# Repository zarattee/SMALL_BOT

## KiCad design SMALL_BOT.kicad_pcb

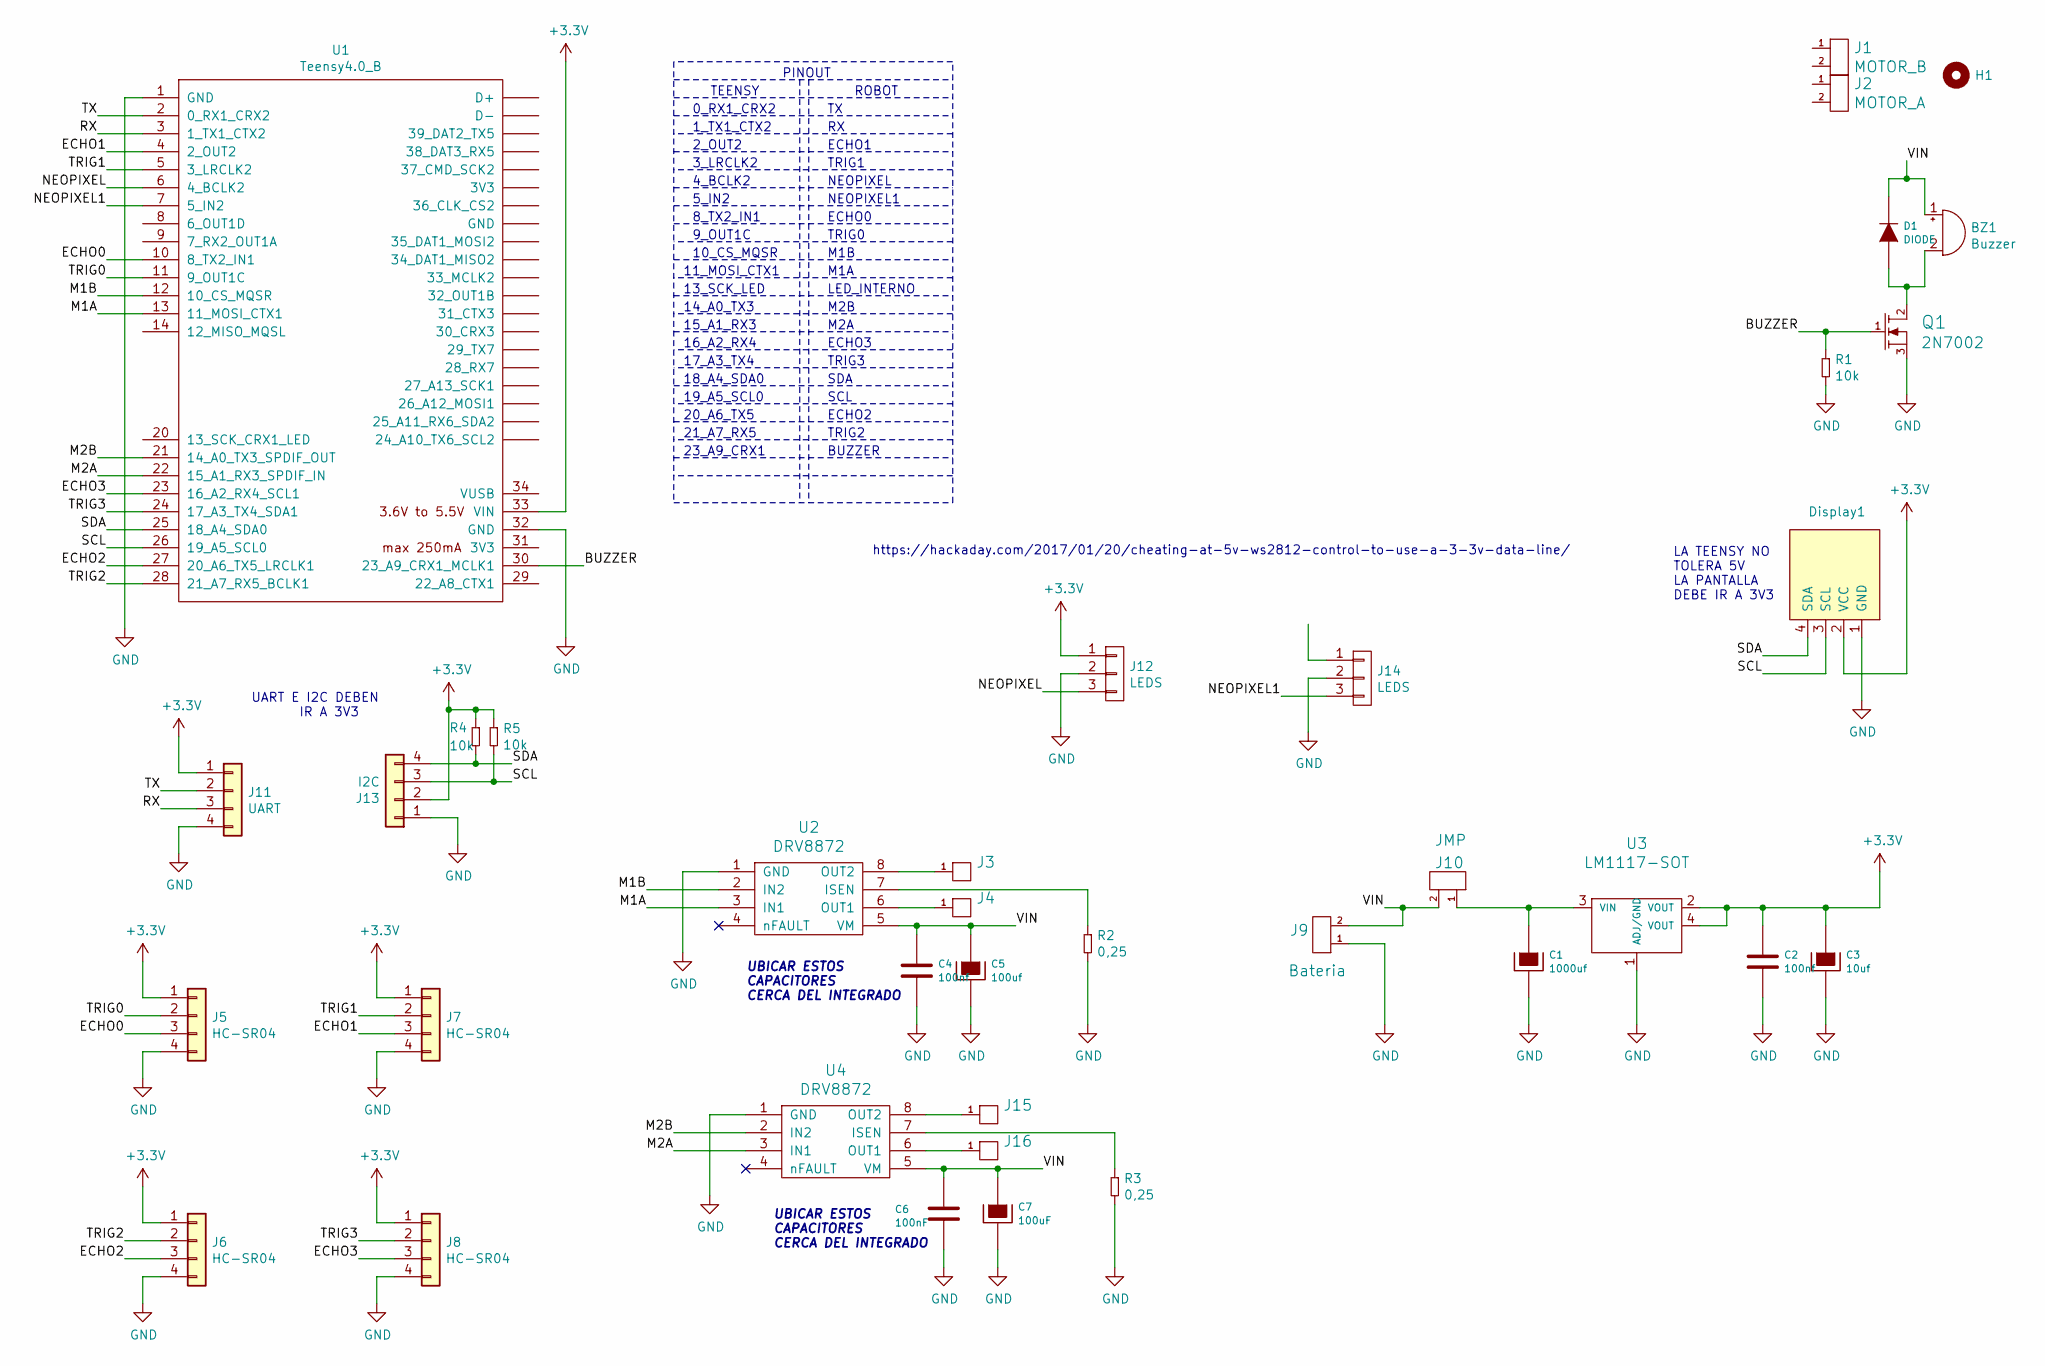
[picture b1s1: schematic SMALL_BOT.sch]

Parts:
BZ1: Buzzer; Buzzer_12mm
C1: 1000uf; CAP_TAN_A
C2, C4: 100nf; C_1206
C3: 10uf; CAP_TAN_A
C5: 100uf; CAP_TAN_A
C6: 100nF; C_1206
C7: 100uF; CAP_TAN_A
D1: DIODE; sod123
Display1: SSD1306-SSD1306-128x64_OLED; 128x64OLED
H1: Mounting_Hole; Bateria_Lipo_2S_800mah
J1: MOTOR_B; Pololu_Micro_Con_Soporte_Simple
J2: MOTOR_A; Pololu_Micro_Con_Soporte_Simple
J3, J4, J15, J16: HEADER_1; Cable_Doble_1,5mm
J5, J6, J7, J8: HC-SR04; pin_strip_4
J9: Bateria; JST_EH_B2B-EH-A_1x02_P2.50mm_Vertical
J10: JMP; Pin_strip_2
J11: UART; pin_strip_4
J12, J14: LEDS; Pin_Strip_3
J13: I2C; pin_strip_4
Q1: 2N7002; SOT23
R1, R4, R5: 10k; R_1206
R2, R3: 0,25; R_1206
U1: Teensy4.0_B; Teensy40_B
U2, U4: DRV8872; SSOP-8
U3: LM1117-SOT; SOT223

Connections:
+3V3: C2.1, C3.1, Display1.2 (VCC), J5.1, J6.1, J7.1, J8.1, J11.1, J12.1, J13.2, R4.1, R5.1, U1.33 (VIN), U3.2 (VOUT), U3.4 (VOUT)
/BUZZER: Q1.1 (G), R1.1, U1.30 (23_A9_CRX1_MCLK1)
/ECHO0: J5.3, U1.10 (8_TX2_IN1)
/ECHO1: J7.3, U1.4 (2_OUT2)
/ECHO2: J6.3, U1.27 (20_A6_TX5_LRCLK1)
/ECHO3: J8.3, U1.23 (16_A2_RX4_SCL1)
/M1A: U1.13 (11_MOSI_CTX1), U2.3 (IN1)
/M1B: U1.12 (10_CS_MQSR), U2.2 (IN2)
/M2A: U1.22 (15_A1_RX3_SPDIF_IN), U4.3 (IN1)
/M2B: U1.21 (14_A0_TX3_SPDIF_OUT), U4.2 (IN2)
/NEOPIXEL: J12.3, U1.6 (4_BCLK2)
/NEOPIXEL1: J14.3, U1.7 (5_IN2)
/RX: J11.3, U1.3 (1_TX1_CTX2)
/SCL: Display1.3 (SCL), J13.3, R5.2, U1.26 (19_A5_SCL0)
/SDA: Display1.4 (SDA), J13.4, R4.2, U1.25 (18_A4_SDA0)
/TRIG0: J5.2, U1.11 (9_OUT1C)
/TRIG1: J7.2, U1.5 (3_LRCLK2)
/TRIG2: J6.2, U1.28 (21_A7_RX5_BCLK1)
/TRIG3: J8.2, U1.24 (17_A3_TX4_SDA1)
/TX: J11.2, U1.2 (0_RX1_CRX2)
/VIN: BZ1.1 (-), C4.1, C5.1, C6.1, C7.1, D1.2 (K), J9.2, J10.2, U2.5 (VM), U4.5 (VM)
GND: C1.2, C2.2, C3.2, C4.2, C5.2, C6.2, C7.2, Display1.1 (GND), J5.4, J6.4, J7.4, J8.4, J9.1, J11.4, J12.2, J13.1, J14.2, Q1.3 (S), R1.2, R2.2, R3.2, U1.1 (GND), U1.32 (GND), U2.1 (GND), U3.1 (ADJ/GND), U4.1 (GND)
unnamed: BZ1.2 (+), D1.1 (A), Q1.2 (D)
unnamed: C1.1, J10.1, U3.3 (VIN)
unnamed: J3.1, U2.8 (OUT2)
unnamed: J4.1, U2.6 (OUT1)
unnamed: J15.1, U4.8 (OUT2)
unnamed: J16.1, U4.6 (OUT1)
unnamed: R2.1, U2.7 (ISEN)
unnamed: R3.1, U4.7 (ISEN)

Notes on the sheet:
PINOUT
TEENSY
ROBOT
0_RX1_CRX2
1_TX1_CTX2
2_OUT2
3_LRCLK2
4_BCLK2
5_IN2
8_TX2_IN1
9_OUT1C
10_CS_MQSR
M1A
M1B
TRIG0
ECHO0
NEOPIXEL1
NEOPIXEL
TRIG1
ECHO1
13_SCK_LED
15_A1_RX3
16_A2_RX4
18_A4_SDA0
19_A5_SCL0
20_A6_TX5
21_A7_RX5
23_A9_CRX1
BUZZER
17_A3_TX4
11_MOSI_CTX1
14_A0_TX3
TRIG2
ECHO2
SCL
SDA
LED_INTERNO
M2B
M2A
ECHO3

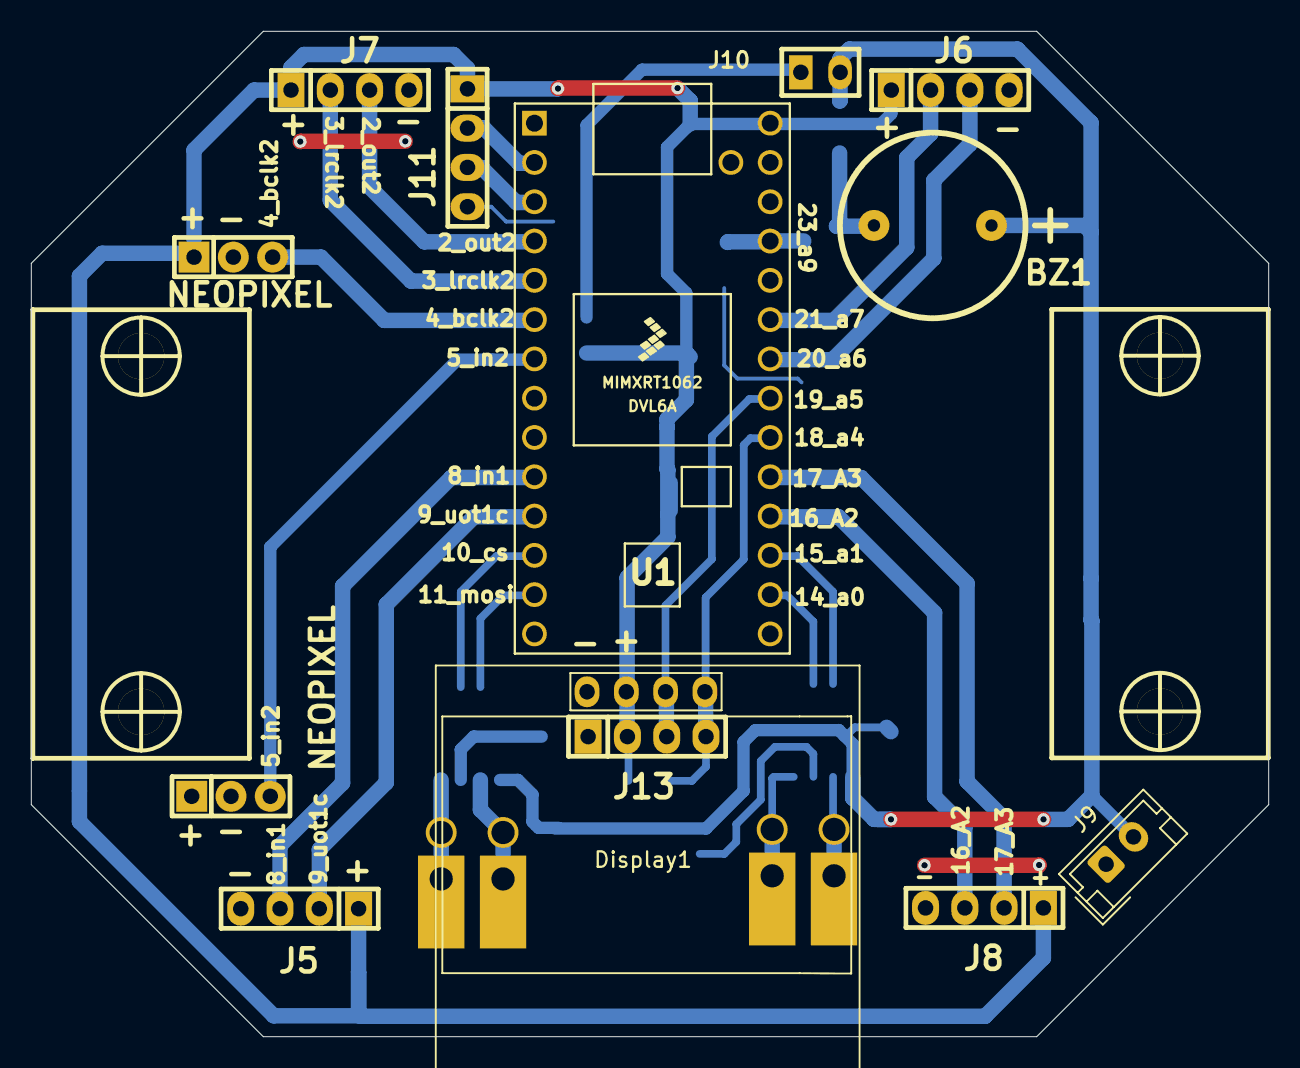
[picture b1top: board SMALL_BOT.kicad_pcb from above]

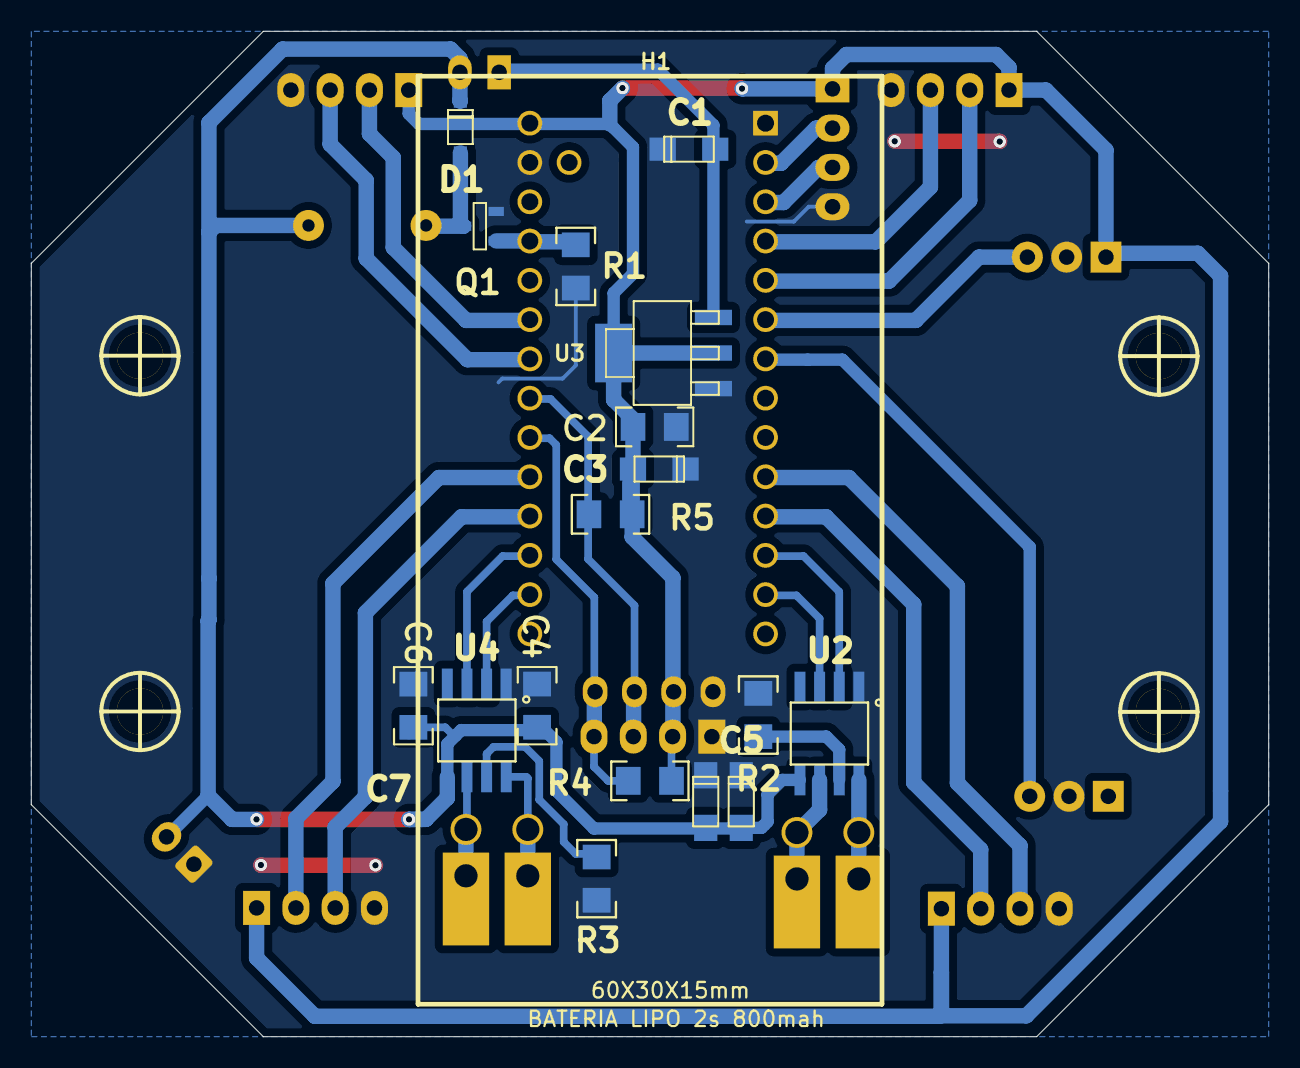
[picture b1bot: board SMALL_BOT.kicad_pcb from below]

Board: 2 copper layers, 80.0 x 65.0 mm, 37 parts (18 on the bottom side), 30 nets.

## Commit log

2020-12-03 COMIIT INICIAL
    INICIO
2020-12-03 MODIFICACION
    SE MOVIO ARCHIVOS
2020-12-03 logo
    se agrego un logo al pcb
2020-12-14 se modifico pcb
    se movieron de lugar los conectores para los sensores ultrasonidos y se agrego pantalla oled
2020-12-14 Varios
    Falta verificar al 100% la compatibilidad con los 3.3v para la Teensy.
2020-12-14 Pantalla Oled
    Actualice la pantalla oled
2020-12-15 modificaciones
    se agrego una brebe pinout, se agrego una carpeta "doc" y lista de materiales, hay que agregarle los precios.tambien se modifico el pcb
2020-12-16 Modelo 3D
    Ajuste el modelo 3D de motor/rueda y el de la bateria. Aún falta contemplar el soporte de la bateria y liberar el espacio debajo de los motores.
2020-12-22 modificacion en el sch
    se acomodo componentes
2020-12-23 se agrego pinout del robot
    se modifico serigrafia y se agrego pinout
2020-12-23 Imagenes ejemplo
    Subo dos imagenes para tomar un ejemplo de los niveladores para que el robot no se incline
2020-12-28 SCH y capacitores
    Genera la version inicial del SCH en pdf y cambie de posición 2 capacitores SMD que estaban debajo de uno de los motores.
2020-12-30 Comentarios en SCH
    Deje algunos comentarios para hacer cambios en el sch para contemplar que la teensy no es tolerante a 5V y las conexiones de los perisfericos deben tener en cuenta ésto.
2020-12-31 modificaciones
    se cambio 5v a 3v3, se movieron los capacitores de los drivers de motores
